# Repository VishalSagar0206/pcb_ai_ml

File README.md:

# PCB DRC Intelligence

Evidence-grounded, LLM-assisted **interpretation and diagnosis** of
deterministic PCB design-rule-check (DRC) violations, extending the
paradigm introduced by *"PCB-QA: Evaluating LLMs over the First Printed
Circuit Board Design Question-Answer Dataset"* from passive PCB question
answering to active diagnosis of real DRC violations.

> **The deterministic KiCad DRC engine is the source of truth for what is
> wrong with a board. The LLM never detects violations -- it interprets,
> contextualizes, and explains violations that KiCad's DRC engine has
> already found, grounded in structured PCB data and retrieved engineering
> knowledge.**

See [ARCHITECTURE.md](ARCHITECTURE.md) for the full system design,
[DESIGN.md](DESIGN.md) for schema/prompt/agent details,
[EVALUATION.md](EVALUATION.md) for the evaluation methodology and current
(demonstration-scale) results, [API.md](API.md) for the HTTP API,
[DEVELOPMENT.md](DEVELOPMENT.md) for setup/testing,
[TESTING_GUIDE.md](TESTING_GUIDE.md) for the full automated + manual/visual
QA checklist (including the frontend), and [EXPERIMENTS.md](EXPERIMENTS.md)
for the ablation/baseline experiment design.

## Pipeline

```
KiCad PCB (.kicad_pcb)
   -> PCB parser -> structured PCB JSON (schema v1.0)
   -> KiCad DRC (kicad-cli, or a recorded fixture for offline use)
   -> violation normalization (taxonomy + uuid-resolved object references)
   -> deterministic PCB context retrieval (minimal per-violation subset)
   -> engineering knowledge RAG (datasheets / guidelines, hybrid retrieval)
   -> LLM reasoning agent (structured JSON output only, json-mode enforced)
   -> evidence validation (rejects/downgrades ungrounded claims)
   -> engineering report + API/CLI
```

## Quick start

```powershell
# 1. Create a venv and install
python -m venv .venv
.venv\Scripts\pip install -e ".[dev]"

# 2. Configure credentials
copy .env.example .env
# edit .env: set CAF_MODEL_BASE_URL / CAF_MODEL_API_KEY / CAF_MODEL_ANALYSIS

# 3. Run the pipeline against the bundled synthetic fixture board
#    (no KiCad installation required -- uses a recorded DRC report)
.venv\Scripts\pcb-ai analyze tests\fixtures\sample_board.kicad_pcb `
    --fixture-drc tests\fixtures\sample_drc_report.json --out results

# 4. Read the generated report
type results\<analysis_id>_report.md
```

If `kicad-cli` (KiCad 7+) is installed and on PATH (or `KICAD_CLI_PATH` is
set), omit `--fixture-drc` to run live DRC.

## Docker (one-command full-stack starter)

```powershell
docker compose up --build
```

Then open http://localhost:8080. This builds and runs both containers:

- **`backend`** (`Dockerfile`) -- the FastAPI app on `:8000`, health-checked
  before the frontend starts.
- **`frontend`** (`frontend/Dockerfile`) -- the production Vite build served
  by nginx on `:8080`, which reverse-proxies `/api/*` to the backend
  container (same-origin from the browser's perspective, so no CORS setup
  is needed at runtime).

Works with **zero configuration** out of the box: if no `.env` exists at
the repo root, `CAF_MODEL_PROVIDER` defaults to `mock` (the offline
`MockLLMProvider`), so the demo/sample boards still fully diagnose without
any credentials. To get **real** LLM diagnosis, copy `.env.example` to
`.env` and either:

- fill in `CAF_MODEL_PROVIDER`/`CAF_MODEL_BASE_URL`/`CAF_MODEL_API_KEY` for
  this project's own gateway, **or**
- set `CAF_MODEL_PROVIDER=gemini` and `GEMINI_API_KEY=<your key>` to test
  with your own free Gemini API key instead (get one in ~30 seconds at
  https://aistudio.google.com/apikey, no credit card needed) -- see
  DEVELOPMENT.md's "Testing with a Gemini API key instead" for how this
  works with zero code changes and without disturbing the config above.

`docker compose` automatically reads that `.env` for variable substitution
into the containers.

KiCad itself is intentionally **not** installed in the backend image (see
DEVELOPMENT.md's "KiCad availability"); the bundled sample boards use
recorded DRC fixtures, so the full pipeline works end-to-end regardless.
`./results` and `./data/pcb_uploads` are mounted as volumes so evaluation
output and uploaded boards survive container restarts.

```powershell
docker compose down          # stop and remove the containers
docker compose logs -f       # follow both services' logs
```

## Windows startup without Docker

If Docker isn't available (or won't run) on a Windows machine, `start.bat`
is a one-command alternative that sets up and runs everything natively:

```powershell
start.bat
```

Double-click it in File Explorer, or run it from a terminal. It checks for
Python 3.10+ and Node.js, creates a virtual environment, installs backend
and frontend dependencies (only on first run), walks you through creating
`.env` with a Gemini API key if one doesn't exist yet, then starts the
backend and frontend each in their own console window and opens the app in
your browser. Safe to run again any time -- it skips work that's already
done and won't start a duplicate server if one's already running.

```powershell
stop.bat   # stops both servers
```

See TESTING_GUIDE.md's "Windows startup without Docker" section for full
details and troubleshooting.

## CLI commands

| Command | Purpose |
|---|---|
| `pcb-ai analyze <board.kicad_pcb>` | Full pipeline: parse -> DRC -> diagnose -> report |
| `pcb-ai drc <board.kicad_pcb>` | Run/normalize DRC only |
| `pcb-ai explain <board.kicad_pcb> --violation <id>` | Diagnose a single violation |
| `pcb-ai report <board.kicad_pcb>` | Print/save the human-readable report |
| `pcb-ai query <board.kicad_pcb> --question "..."` | Free-form Q&A via tool-calling agent |
| `pcb-ai index-knowledge <dir>` | Ingest datasheets/guidelines into a persisted chunk index |
| `pcb-ai evaluate <evaluation_dir>` | Run baseline/ablation experiments (Phase 17-20) |
| `pcb-ai doctor` | Report kicad-cli/LLM/knowledge-dir environment status |

All commands accept `--fixture-drc <path>` to use a recorded DRC JSON
report instead of invoking `kicad-cli` (useful when KiCad isn't installed).

## Running the API

```powershell
.venv\Scripts\uvicorn pcb_ai.api.app:app --host 0.0.0.0 --port 8000
```

See [API.md](API.md) for endpoints.

## Frontend (visual showcase)

A React + TypeScript + Tailwind + Framer Motion + Recharts dashboard lives in
[frontend/](frontend). It provides a dashboard-style Board Explorer (live
stat cards + an interactive PCB canvas with real component/pad/track/via/
zone coordinates and DRC violations highlighted in place, paired with an
evidence-grounded diagnosis panel), an animated pipeline architecture
explainer, a Knowledge Base tab demonstrating the hybrid-retrieval RAG
layer against real component datasheets (curated from
[pcb_qa-4FEE](pcb_qa-4FEE), ~300 chunks / 12 real manufacturer PDFs, with
live search), an evaluation dashboard driven by real ablation results, and
a research-lineage section referencing the same reference benchmark.

```powershell
# Terminal 1: backend
.venv\Scripts\uvicorn pcb_ai.api.app:app --host 127.0.0.1 --port 8931

# Terminal 2: frontend
cd frontend
npm install
npm run dev
```

Open http://localhost:5173/. See [frontend/README.md](frontend/README.md)
for details.

## Repository layout

```
src/pcb_ai/
  schemas/        Versioned pydantic schemas (PCB, DRC, diagnosis, knowledge, context)
  parser/         .kicad_pcb -> structured PCB JSON
  drc/            kicad-cli invocation + DRC JSON normalization
  context/        PCB relationship graph + per-violation context retriever
  rag/            Document chunking + hybrid (BM25 + TF-IDF) knowledge retriever
  llm/            Provider-agnostic LLM interface + OpenAI-compatible adapter + mock
  prompts/        Versioned prompts
  agent/          Multi-stage diagnosis pipeline + tool registry + interactive query agent
  severity/       Deterministic severity policy
  validation/     Evidence validator (Phase 12)
  reporting/      Human-readable engineering report generator
  eval/           Baseline/ablation experiments + metrics + runner
  api/            FastAPI app
  cli/            Typer CLI
  observability/  Logging + trace recording
  service.py      End-to-end orchestration used by both API and CLI
tests/            Unit/integration/e2e tests + fixtures (sample board, DRC report,
                  knowledge/datasheet documents, a demo evaluation dataset)
```

## Known limitations (see docs for detail)

- No KiCad installation is available in the development environment used to
  build this; DRC integration was validated against recorded fixtures and
  the real `kicad-cli pcb drc --format json` schema (documented from
  authoritative sources), not a live KiCad process. See
  [DEVELOPMENT.md](DEVELOPMENT.md).
- The "semantic" vector retrieval backend is TF-IDF, not a trained
  embedding model (no embedding endpoint was available); see
  [DESIGN.md](DESIGN.md).
- The evaluation results in [EVALUATION.md](EVALUATION.md) are from one
  small synthetic demonstration board, not a validated research-scale
  dataset. No accuracy claims beyond this demo run are made.

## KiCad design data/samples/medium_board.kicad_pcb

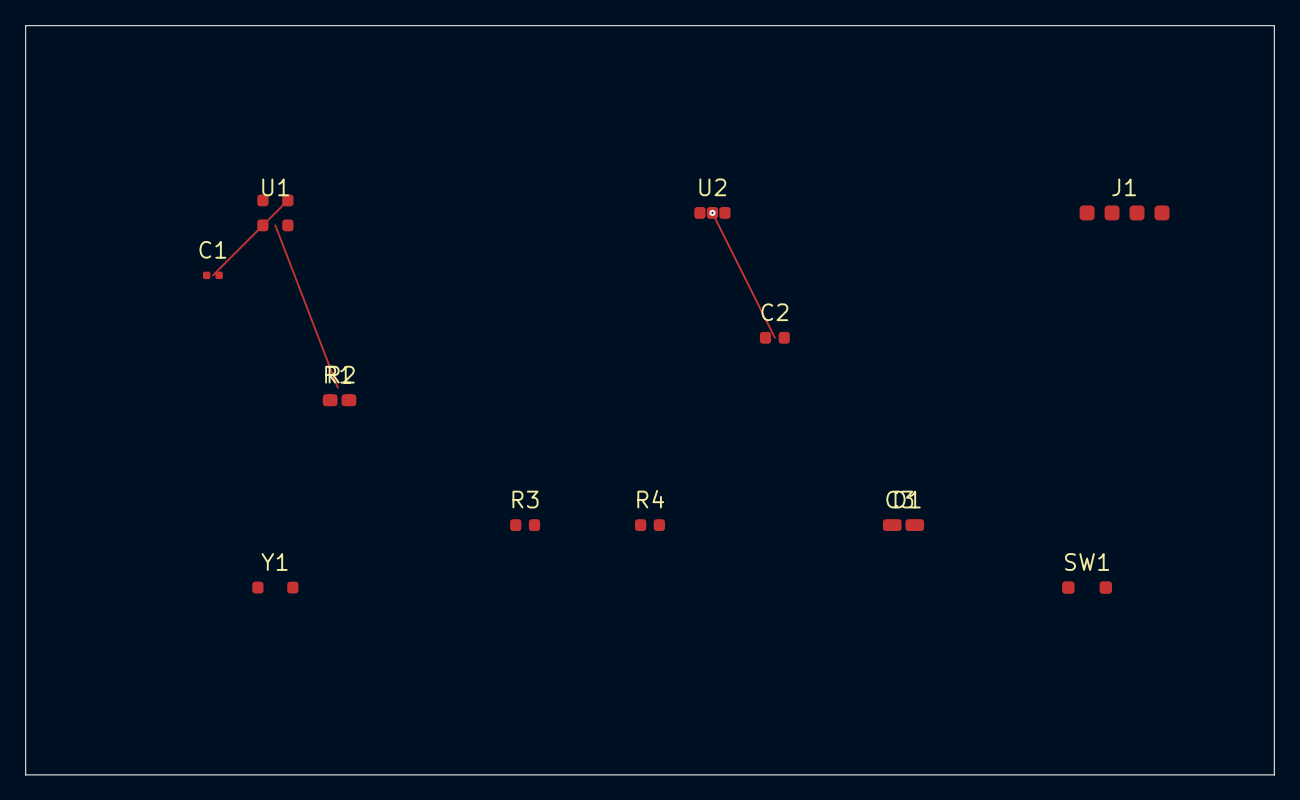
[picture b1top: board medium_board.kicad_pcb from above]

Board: 2 copper layers, 100.0 x 60.0 mm, 13 parts (0 on the bottom side), 8 nets.

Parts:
C1: 100nF; C_0402_1005Metric
C2: 1uF; C_0603_1608Metric
C3: 10uF; C_0805_2012Metric
D1: SS14; D_SOD-123
J1: Header_4Pin; PinHeader_1x04_P2.54mm
R1, R2: 10k; R_0603_1608Metric
R3, R4: 4k7; R_0603_1608Metric
SW1: SW_RESET; SW_SPST_TL3342
U1: MCU_ARM32; QFN-32_5x5mm_P0.5mm
U2: AP2112K-3.3; SOT-23-5
Y1: 16MHz; Crystal_SMD_3225-4Pin_3.2x2.5mm

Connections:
3V3: C3.1, D1.2
GND: C1.2, C2.2, C3.2, J1.2, SW1.2, U1.2, U2.2
RESET: R4.1, SW1.1
SPI_CLK: R1.1, U1.3
SPI_MOSI: R2.1, U1.4
VCC: C1.1, J1.1, R1.2, R2.2, R3.2, R4.2, U1.1
VIN: D1.1, U2.1
VOUT: C2.1, U2.3

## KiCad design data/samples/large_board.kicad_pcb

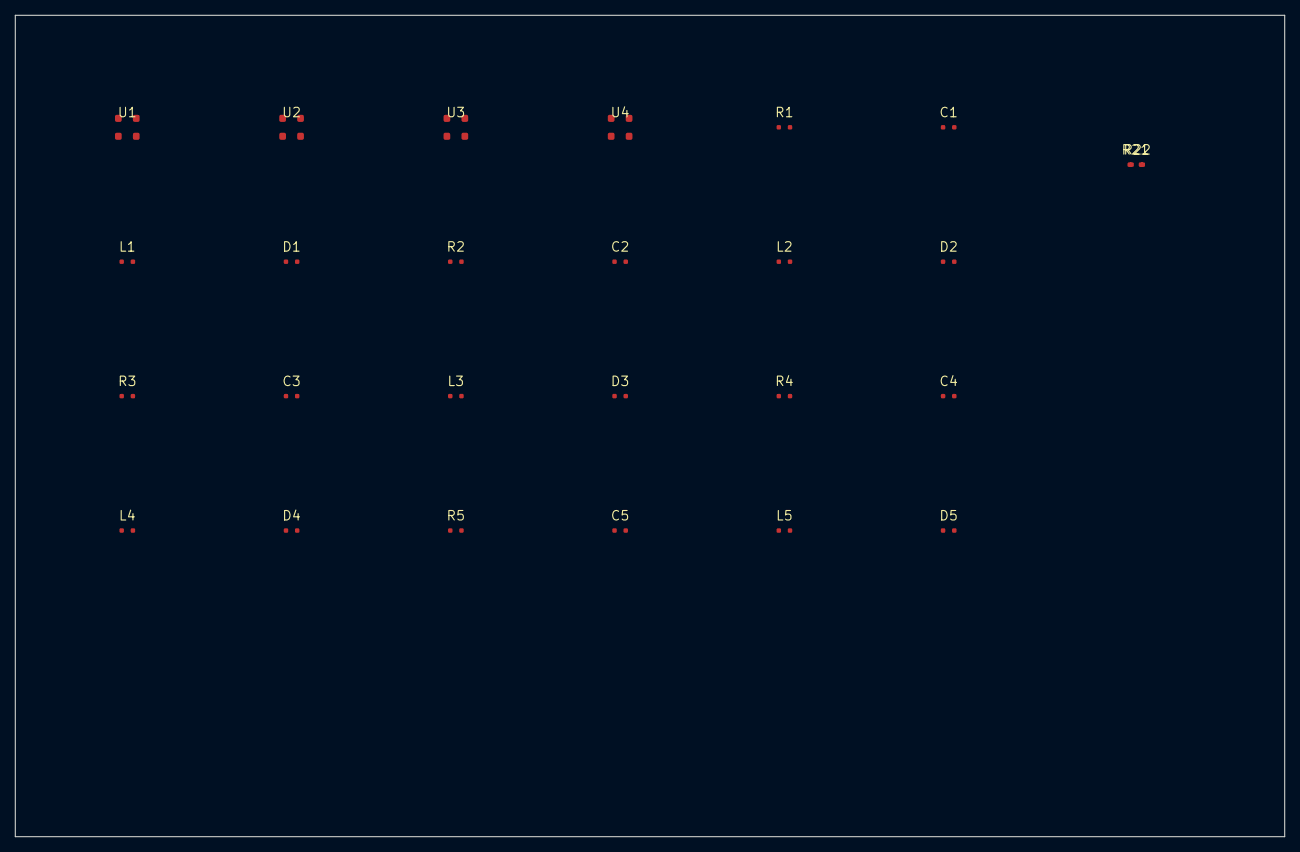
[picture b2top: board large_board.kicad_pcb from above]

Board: 2 copper layers, 170.0 x 110.0 mm, 26 parts (0 on the bottom side), 2 nets, no tracks yet.

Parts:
C1, C2, C3, C4, C5: 100nF; C_0402_1005Metric
D1, D2, D3, D4, D5: SS14; D_SOD-123
L1, L2, L3, L4, L5: 10uH; L_0805_2012Metric
R1, R2, R3, R4, R5: 10k; R_0603_1608Metric
R21, R22: 1k; R_0603_1608Metric
U1: MCU_ARM32; QFN-32_5x5mm_P0.5mm
U2: FLASH_W25Q; SOIC-8_3.9x4.9mm_P1.27mm
U3: GYRO_MPU6050; LGA-16_3x3mm_P0.5mm
U4: USB_HUB; TSSOP-24_4.4x7.8mm_P0.65mm

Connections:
GND: U1.3, U2.3, U3.3, U4.3
VCC: C1.2, C2.2, C3.2, C4.2, C5.2, D1.2, D2.2, D3.2, D4.2, D5.2, L1.2, L2.2, L3.2, L4.2, L5.2, R1.2, R2.2, R3.2, R4.2, R5.2, R21.2, R22.2, U1.2, U2.2, U3.2, U4.2

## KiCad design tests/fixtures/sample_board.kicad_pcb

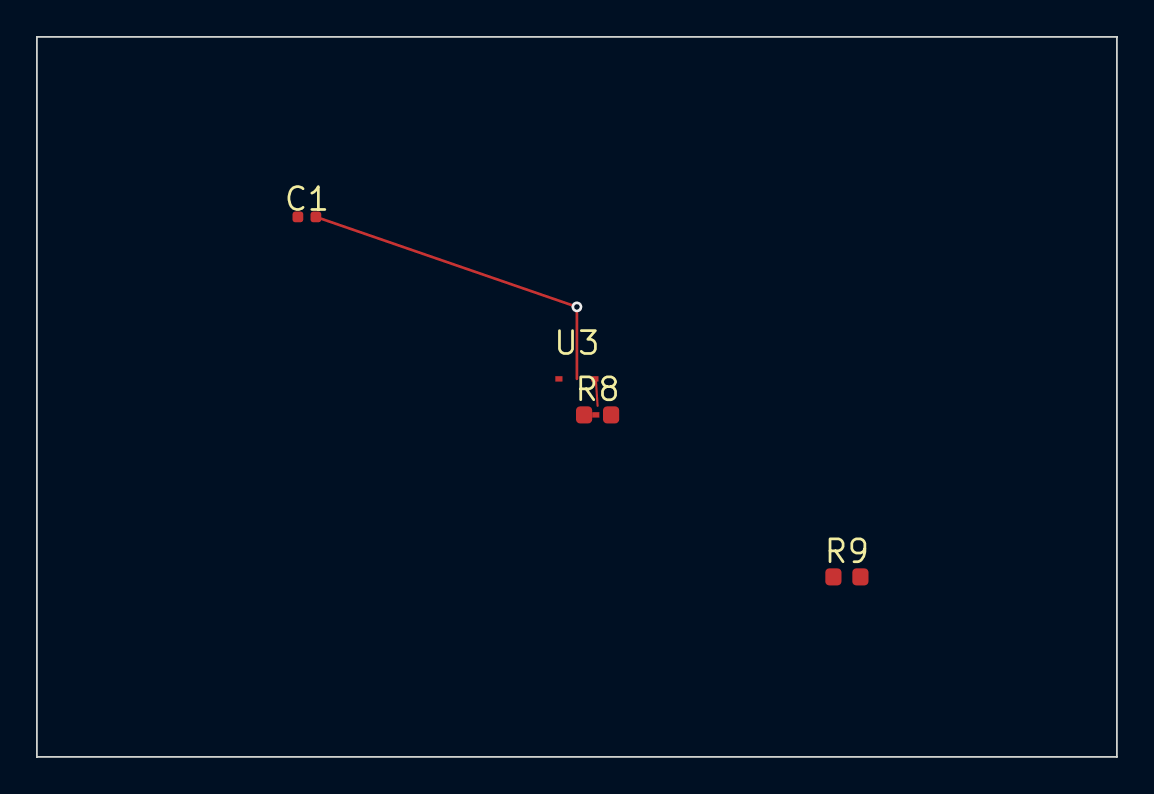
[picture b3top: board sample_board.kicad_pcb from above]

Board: 2 copper layers, 60.0 x 40.0 mm, 4 parts (0 on the bottom side), 4 nets.

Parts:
C1: 100nF; C_0402_1005Metric
R8: 10k; R_0603_1608Metric
R9: 4k7; R_0603_1608Metric
U3: MCU_XYZ; QFN-32_5x5mm_P0.5mm

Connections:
GND: C1.2, U3.2
SPI_CLK: R8.1, U3.4
SPI_MISO: R8.2, R9.1
VCC: C1.1, U3.1
